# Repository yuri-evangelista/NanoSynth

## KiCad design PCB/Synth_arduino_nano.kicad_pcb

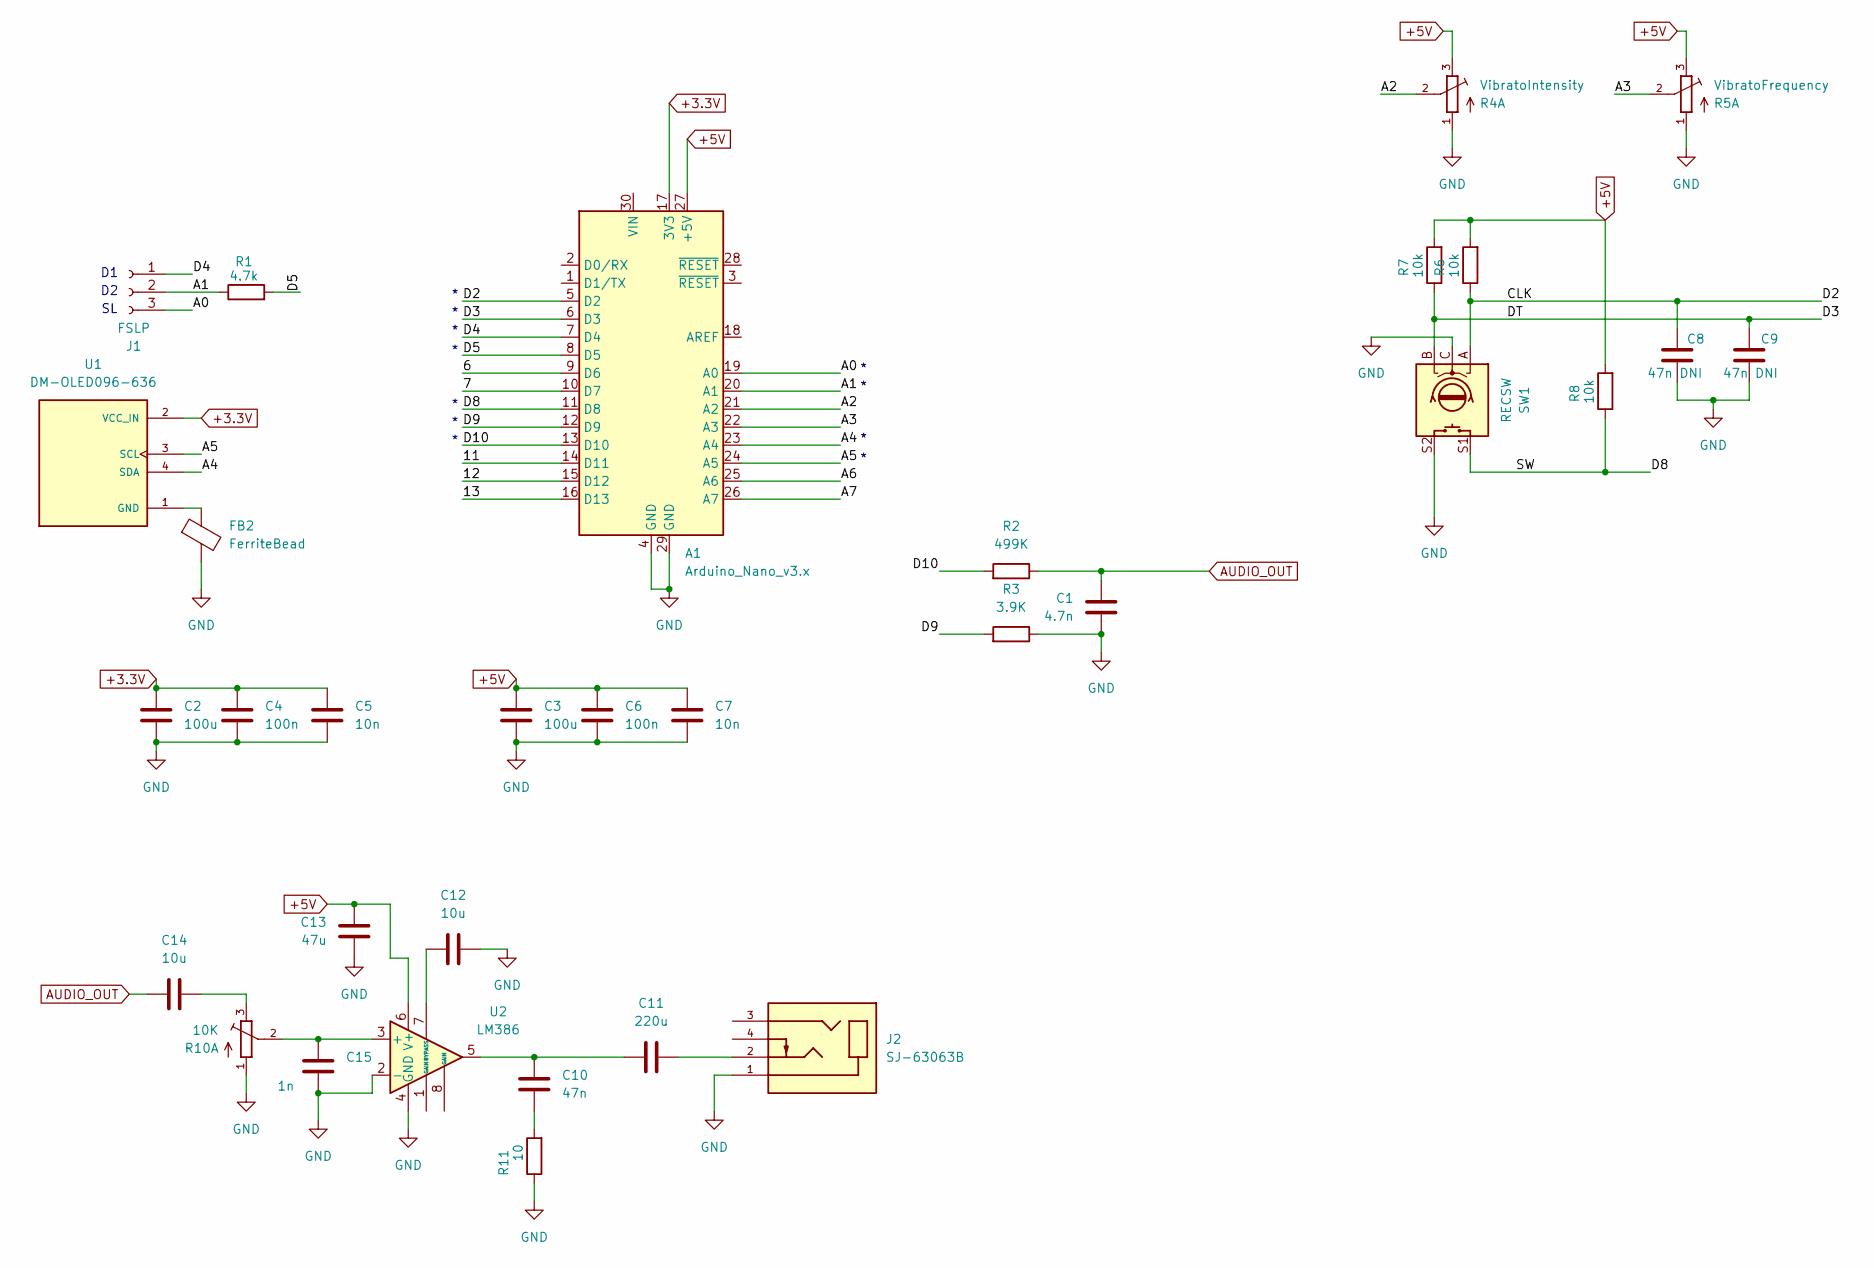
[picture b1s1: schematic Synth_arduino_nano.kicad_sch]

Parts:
A1: Arduino_Nano_v3.x; Arduino_Nano
C1: 4.7n; C_0603_1608Metric_Pad1.08x0.95mm_HandSolder
C2, C3: 100u; C_1206_3216Metric_Pad1.33x1.80mm_HandSolder
C4, C6: 100n; C_0603_1608Metric_Pad1.08x0.95mm_HandSolder
C5, C7: 10n; C_0603_1608Metric_Pad1.08x0.95mm_HandSolder
C8, C9: 47n DNI; C_0603_1608Metric_Pad1.08x0.95mm_HandSolder
C10: 47n; C_0603_1608Metric_Pad1.08x0.95mm_HandSolder
C11: 220u; C_1206_3216Metric_Pad1.33x1.80mm_HandSolder
C12, C14: 10u; C_1206_3216Metric_Pad1.33x1.80mm_HandSolder
C13: 47u; C_1206_3216Metric_Pad1.33x1.80mm_HandSolder
C15: 1n; C_0603_1608Metric_Pad1.08x0.95mm_HandSolder
FB2: FerriteBead; L_0603_1608Metric_Pad1.05x0.95mm_HandSolder
J1: FSLP; Pololu FSLP 100
J2: SJ-63063B; CUI_SJ-63063B; PARTREV 1.0
R1: 4.7k; R_0805_2012Metric_Pad1.20x1.40mm_HandSolder
R2: 499K; R_0805_2012Metric_Pad1.20x1.40mm_HandSolder
R3: 3.9K; R_0805_2012Metric_Pad1.20x1.40mm_HandSolder
R4: VibratoIntensity; PTV09A-4025F-B103
R5: VibratoFrequency; PTV09A-4025F-B103
R6, R7, R8: 10k; R_0805_2012Metric_Pad1.20x1.40mm_HandSolder
R10: 10K; PTV09A-4025F-B103
R11: 10; R_0805_2012Metric_Pad1.20x1.40mm_HandSolder
SW1: RECSW; RotaryEncoder_Alps_EC12E-Switch_Vertical_H20mm
U1: DM-OLED096-636; MODULE_DM-OLED096-636; PARTREV 2018-09-10
U2: LM386; DIP-8_W7.62mm

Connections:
+3.3V: A1.17 (3V3), C2.1, C4.1, C5.1, U1.2 (VCC_IN)
+5V: A1.27 (+5V), C3.1, C6.1, C7.1, C13.2, R4.3, R5.3, R6.2, R7.2, R8.2, U2.6 (V+)
/6: A1.9 (D6)
/7: A1.10 (D7)
/11: A1.14 (D11)
/12: A1.15 (D12)
/13: A1.16 (D13)
/A0: A1.19 (A0), J1.3
/A1: A1.20 (A1), J1.2, R1.1
/A2: A1.21 (A2), R4.2
/A3: A1.22 (A3), R5.2
/A4: A1.23 (A4), U1.4 (SDA)
/A5: A1.24 (A5), U1.3 (SCL)
/A6: A1.25 (A6)
/A7: A1.26 (A7)
/CLK: A1.5 (D2), C8.1, R6.1, SW1.A
/D3: A1.6 (D3), C9.1, R7.1, SW1.B
/D4: A1.7 (D4), J1.1
/D5: A1.8 (D5), R1.2
/D8: A1.11 (D8), R8.1, SW1.S1
/D9: A1.12 (D9), R3.2
/D10: A1.13 (D10), R2.2
AUDIO_OUT: C1.1, C14.1, R2.1
GND: A1.4 (GND), A1.29 (GND), C1.2, C2.2, C3.2, C4.2, C5.2, C6.2, C7.2, C8.2, C9.2, C12.2, C13.1, C15.2, FB2.2, J2.1, R3.1, R4.1, R5.1, R10.1, R11.1, SW1.C, SW1.S2, U2.2 (-), U2.4 (GND)
unnamed: C10.1, C11.1, U2.5
unnamed: C10.2, R11.2
unnamed: C11.2, J2.2
unnamed: C14.2, R10.3
unnamed: FB2.1, U1.1 (GND)
unnamed: C15.1, R10.2, U2.3 (+)
unnamed: C12.1, U2.7 (BYPASS)

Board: 2 copper layers, 32 parts (6 on the bottom side), 24 nets, no tracks yet.

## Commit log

2025-12-19 Create butta
2025-12-19 Create _
2025-12-22 fixed a few things
    used delays in control loop
    changed the oscillators and reduced their number
